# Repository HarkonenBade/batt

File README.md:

# Batt

A simple and compact TP4056 based LiPo charge and protection board.

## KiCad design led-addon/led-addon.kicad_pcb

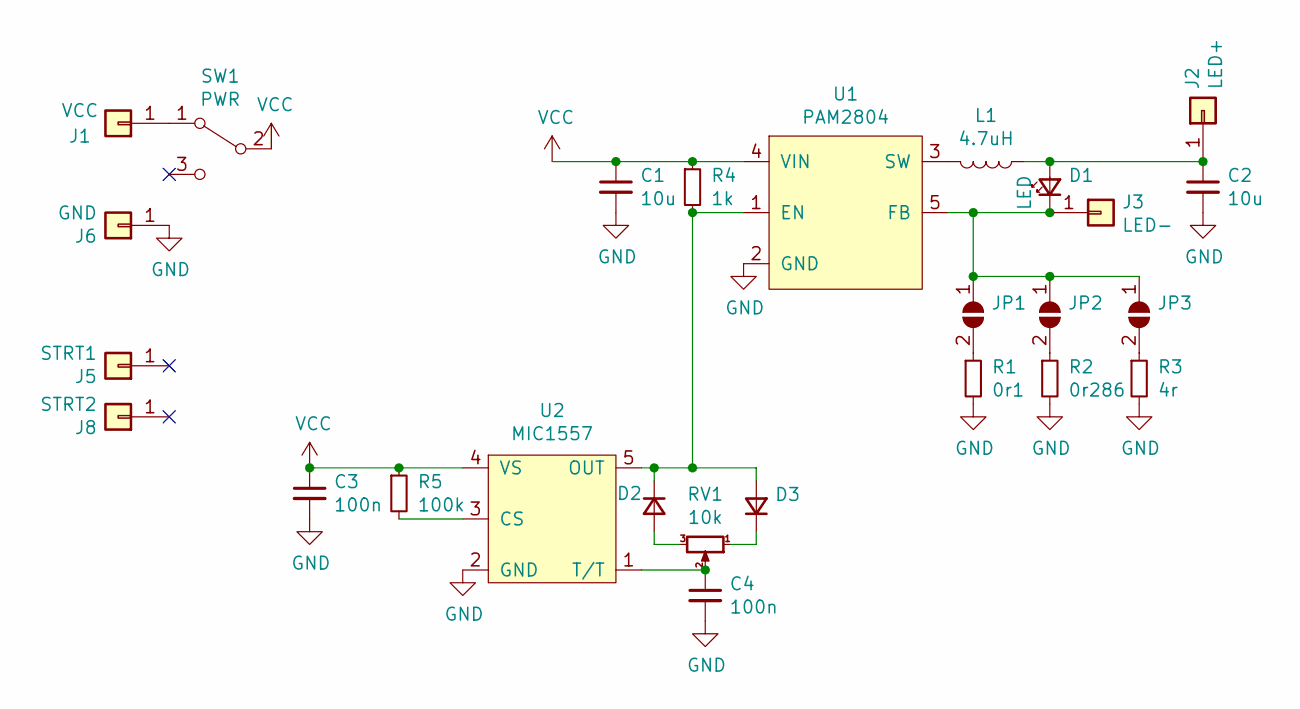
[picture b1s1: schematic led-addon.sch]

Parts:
C1, C2: 10u; C_0603_1608Metric
C3, C4: 100n; C_0603_1608Metric
D1: LED; JST_PH_B2B-PH-K_1x02_P2.00mm_Vertical
D2, D3: D_SOD-523
J1: VCC; PinHeader_1x01_P2.54mm_Vertical_nosilk
J2: LED+; PinHeader_1x01_P2.54mm_Vertical_nosilk
J3: LED-; PinHeader_1x01_P2.54mm_Vertical_nosilk
J5: STRT1; PinHeader_1x01_P2.54mm_Vertical_nosilk
J6: GND; PinHeader_1x01_P2.54mm_Vertical_nosilk
J8: STRT2; PinHeader_1x01_P2.54mm_Vertical_nosilk
JP1, JP2, JP3: SolderJumper-2_P1.3mm_Open_Pad1.0x1.5mm
L1: 4.7uH; L_1008_2520Metric
R1: 0r1; R_0805_2012Metric
R2: 0r286; R_0805_2012Metric
R3: 4r; R_0805_2012Metric
R4: 1k; R_0603_1608Metric
R5: 100k; R_0603_1608Metric
RV1: 10k; PinHeader_1x03_P2.54mm_Vertical
SW1: PWR; PinHeader_1x03_P2.54mm_Vertical
U1: PAM2804; TSOT-23-5
U2: MIC1557; SOT-23-5

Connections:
GND: C1.2, C2.2, C3.2, C4.2, J6.1, R1.2, R2.2, R3.2, U1.2 (GND), U2.2 (GND)
unnamed: C2.1, D1.1 (A), J2.1, L1.1
unnamed: C4.1, RV1.2, U2.1 (T/T)
unnamed: D1.2 (K), J3.1, JP1.1 (A), JP2.1 (A), JP3.1 (A), U1.5 (FB)
unnamed: D2.1 (K), D3.2 (A), R4.2, U1.1 (EN), U2.5 (OUT)
unnamed: D2.2 (A), RV1.3
unnamed: D3.1 (K), RV1.1
unnamed: J1.1, SW1.1 (A)
unnamed: JP1.2 (B), R1.1
unnamed: JP2.2 (B), R2.1
unnamed: JP3.2 (B), R3.1
unnamed: L1.2, U1.3 (SW)
unnamed: R5.2, U2.3 (CS)
VCC: C1.1, C3.1, R4.1, R5.1, SW1.2 (B), U1.4 (VIN), U2.4 (VS)

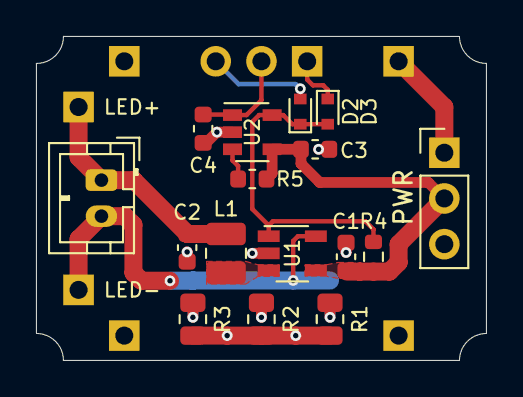
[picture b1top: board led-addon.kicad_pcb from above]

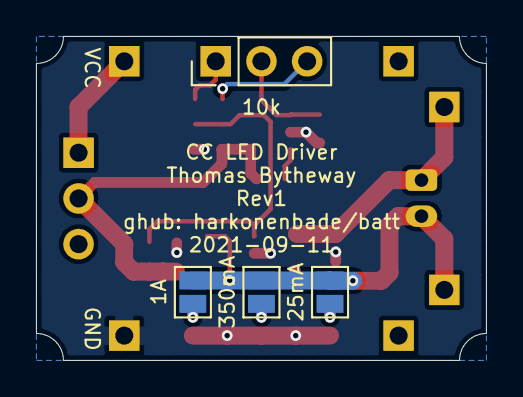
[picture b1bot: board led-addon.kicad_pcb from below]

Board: 2 copper layers, 25.0 x 18.0 mm, 26 parts (4 on the bottom side), 14 nets.

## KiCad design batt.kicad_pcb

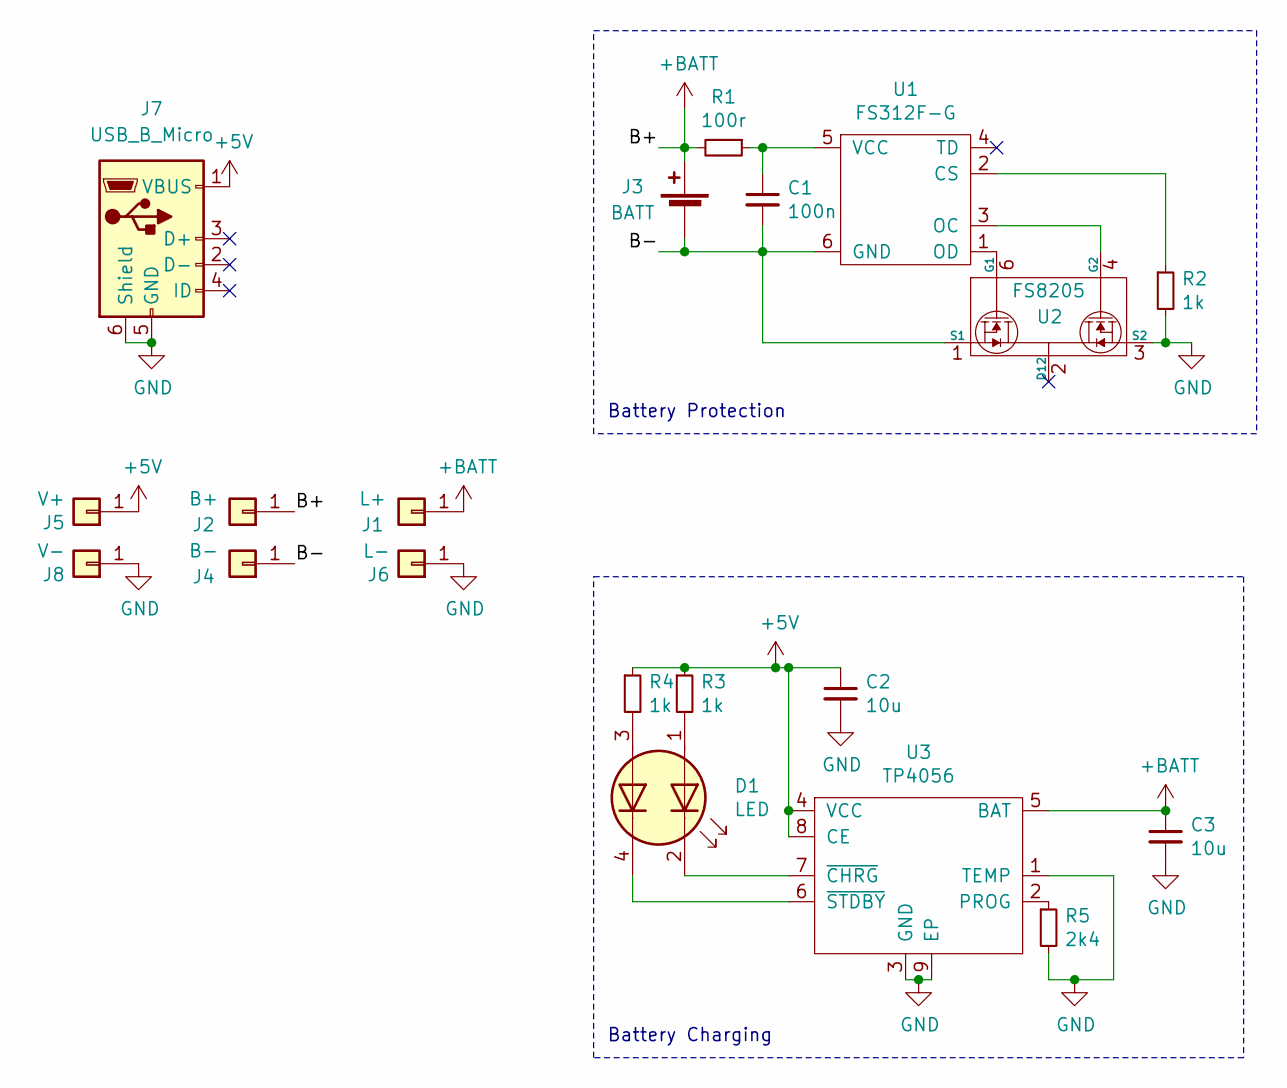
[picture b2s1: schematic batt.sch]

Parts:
C1: 100n; C_0603_1608Metric; LCSC C80516
C2, C3: 10u; C_0805_2012Metric; LCSC C17024
D1: LED; TJ-S1615SW6TGLCRG-A5; LCSC C273605
J1: L+; PinHeader_1x01_P2.54mm_Vertical_nosilk
J2: B+; PinHeader_1x01_P2.54mm_Vertical_nosilk
J3: BATT; JST_PH_S2B-PH-K_1x02_P2.00mm_Horizontal
J4: B-; PinHeader_1x01_P2.54mm_Vertical_nosilk
J5: V+; PinHeader_1x01_P2.54mm_Vertical_nosilk
J6: L-; PinHeader_1x01_P2.54mm_Vertical_nosilk
J7: USB_B_Micro; U254-051T-4BH83-F1S; LCSC C397452
J8: V-; PinHeader_1x01_P2.54mm_Vertical_nosilk
R1: 100r; R_0603_1608Metric; LCSC C163844
R2, R3, R4: 1k; R_0603_1608Metric; LCSC C115325
R5: 2k4; R_0603_1608Metric; LCSC C294654
U1: FS312F-G; SOT-23-6; LCSC C82736
U2: FS8205; SOT-23-6; LCSC C32254
U3: TP4056; HSOP-8-1EP_3.9x4.9mm_P1.27mm_EP2.41x3.1mm; LCSC C382139

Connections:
+5V: C2.1, J5.1, J7.1 (VBUS), R3.1, R4.1, U3.4 (VCC), U3.8 (CE)
+BATT: C3.1, J1.1, J2.1, J3.1 (+), R1.2, U3.5 (BAT)
/B-: C1.2, J3.2 (-), J4.1, U1.6 (GND), U2.1 (S1)
GND: C2.2, C3.2, J6.1, J7.5 (GND), J7.6 (Shield), J8.1, R2.2, R5.2, U2.3 (S2), U3.1 (TEMP), U3.3 (GND), U3.9 (EP)
unnamed: C1.1, R1.1, U1.5 (VCC)
unnamed: D1.1 (A1), R3.2
unnamed: D1.2 (K1), U3.7 (~CHRG)
unnamed: D1.3 (A2), R4.2
unnamed: D1.4 (K2), U3.6 (~STDBY)
unnamed: R2.1, U1.2 (CS)
unnamed: R5.1, U3.2 (PROG)
unnamed: U1.1 (OD), U2.6 (G1)
unnamed: U1.3 (OC), U2.4 (G2)
unnamed: U2.2 (D12), U2.5 (D12)

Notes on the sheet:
Battery Protection
Battery Charging

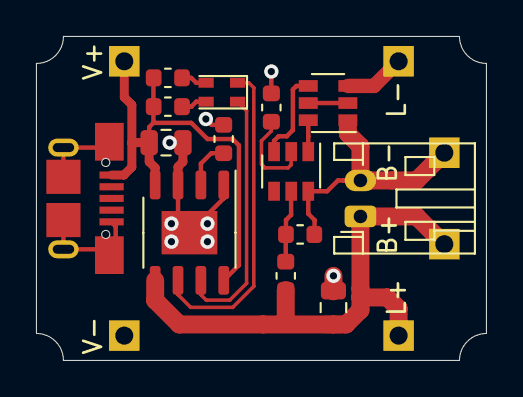
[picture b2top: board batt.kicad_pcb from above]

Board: 2 copper layers, 25.0 x 18.0 mm, 20 parts (0 on the bottom side), 14 nets.

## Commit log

2020-09-20 Base board design
2020-09-20 Add licence
2020-09-22 Various tweaks to schematic
2020-09-22 Schematic and Board snapshots
2020-10-03 Aux origin on PCB
2021-09-18 New directory structure for additional related boards
2021-09-18 LED addon board
2021-09-18 LED addon gerbers
2021-09-18 Doc pages and script
2021-09-19 Fix doc pages
